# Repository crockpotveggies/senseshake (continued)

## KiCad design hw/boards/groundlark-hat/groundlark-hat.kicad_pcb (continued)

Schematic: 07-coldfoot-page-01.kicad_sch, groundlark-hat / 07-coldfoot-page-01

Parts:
C60, C61: 10u; Capacitor_SMD__C_0805_2012Metric; MPN GRM21BR61A106KE19L
C62, C67: 100n; Capacitor_SMD__C_0603_1608Metric; MPN GRM188R71H104KA93D
C63, C64, C65, C66: 22u; Capacitor_SMD__C_1206_3216Metric; MPN GRM31CR61A226KE19L
J5: Coldfoot run-1 1x1; Coldfoot_Run1_70DS; MPN HC-PBB40C-70DS-0.4V-3.0-02
L1: 4.7uH; Inductor_SMD__L_Bourns_SRN6045TA; MPN SRN6045TA-4R7M
R60: 0.1; Resistor_SMD__R_1206_3216Metric; MPN ERJ-8CWFR100V
U50: AP63203WU-7; Package_TO_SOT_SMD__TSOT-23-6; MPN AP63203WU-7

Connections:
28: J5.28 (analog[1].pad)
29: J5.29 (analog[0].pad)
CF_3V3: C66.1, C67.1, J5.9 (dvdd_pads[5].pad), J5.11 (vdd_pads[1].pad), J5.19 (dvdd_pads[4].pad), J5.24 (dvdd_pads[3].pad), J5.44 (dvdd_pads[2].pad), J5.46 (vdd_pads[0].pad), J5.54 (dvdd_pads[1].pad), J5.62 (dvdd_pads[0].pad), R60.2; also elsewhere on the board
CF_BIDIR_2: J5.4 (bidir[2].pad); also elsewhere on the board
CF_BIDIR_3: J5.3 (bidir[3].pad); also elsewhere on the board
CF_BIDIR_4: J5.2 (bidir[4].pad); also elsewhere on the board
CF_BIDIR_5: J5.1 (bidir[5].pad); also elsewhere on the board
CF_BIDIR_6: J5.70 (bidir[6].pad); also elsewhere on the board
CF_BIDIR_7: J5.69 (bidir[7].pad); also elsewhere on the board
CF_BIDIR_8: J5.68 (bidir[8].pad); also elsewhere on the board
CF_BIDIR_9: J5.67 (bidir[9].pad); also elsewhere on the board
CF_BIDIR_10: J5.66 (bidir[10].pad); also elsewhere on the board
CF_BIDIR_11: J5.65 (bidir[11].pad); also elsewhere on the board
CF_BIDIR_12: J5.64 (bidir[12].pad); also elsewhere on the board
CF_BIDIR_13: J5.63 (bidir[13].pad); also elsewhere on the board
CF_BIDIR_14: J5.60 (bidir[14].pad); also elsewhere on the board
CF_BIDIR_15: J5.59 (bidir[15].pad); also elsewhere on the board
CF_BIDIR_16: J5.58 (bidir[16].pad); also elsewhere on the board
CF_BIDIR_17: J5.57 (bidir[17].pad); also elsewhere on the board
CF_BIDIR_18: J5.56 (bidir[18].pad); also elsewhere on the board
CF_BIDIR_19: J5.55 (bidir[19].pad); also elsewhere on the board
CF_BIDIR_20: J5.52 (bidir[20].pad); also elsewhere on the board
CF_BIDIR_21: J5.51 (bidir[21].pad); also elsewhere on the board
CF_BIDIR_22: J5.50 (bidir[22].pad); also elsewhere on the board
CF_BIDIR_23: J5.49 (bidir[23].pad); also elsewhere on the board
CF_BIDIR_24: J5.48 (bidir[24].pad); also elsewhere on the board
CF_BIDIR_25: J5.47 (bidir[25].pad); also elsewhere on the board
CF_BIDIR_26: J5.43 (bidir[26].pad); also elsewhere on the board
CF_BIDIR_27: J5.42 (bidir[27].pad); also elsewhere on the board
CF_BIDIR_28: J5.41 (bidir[28].pad); also elsewhere on the board
CF_BIDIR_29: J5.40 (bidir[29].pad); also elsewhere on the board
CF_BIDIR_30: J5.39 (bidir[30].pad); also elsewhere on the board
CF_BIDIR_31: J5.38 (bidir[31].pad); also elsewhere on the board
CF_BIDIR_32: J5.37 (bidir[32].pad); also elsewhere on the board
CF_BIDIR_33: J5.36 (bidir[33].pad); also elsewhere on the board
CF_BIDIR_34: J5.35 (bidir[34].pad); also elsewhere on the board
CF_BIDIR_35: J5.34 (bidir[35].pad); also elsewhere on the board
CF_BIDIR_36: J5.33 (bidir[36].pad); also elsewhere on the board
CF_BIDIR_37: J5.32 (bidir[37].pad); also elsewhere on the board
CF_BIDIR_38: J5.31 (bidir[38].pad); also elsewhere on the board
CF_BIDIR_39: J5.30 (bidir[39].pad); also elsewhere on the board
CF_BST: C62.1, U50.6 (BST)
CF_IN_1: J5.26 (inputs[1].pad); also elsewhere on the board
CF_IN_2: J5.23 (inputs[2].pad); also elsewhere on the board
CF_IN_4: J5.21 (inputs[4].pad); also elsewhere on the board
CF_IN_5: J5.20 (inputs[5].pad); also elsewhere on the board
CF_IN_6: J5.17 (inputs[6].pad); also elsewhere on the board
CF_IN_7: J5.16 (inputs[7].pad); also elsewhere on the board
CF_IN_8: J5.15 (inputs[8].pad); also elsewhere on the board
CF_IN_9: J5.14 (inputs[9].pad); also elsewhere on the board
CF_IN_10: J5.13 (inputs[10].pad); also elsewhere on the board
CF_IN_11: J5.12 (inputs[11].pad); also elsewhere on the board
CF_MESH_CLK: J5.8 (clk_pad); also elsewhere on the board
CF_REG_3V3: C63.1, C64.1, C65.1, L1.2, R60.1, U50.1 (FB)
CF_RESET_N: J5.7 (rst_n_pad); also elsewhere on the board
CF_SW: C62.2, L1.1, U50.5 (SW)
CF_TELEMETRY: J5.5 (bidir[1].pad)
CF_TILE_CLK: J5.22 (inputs[3].pad); also elsewhere on the board
CF_UART_RX: J5.27 (inputs[0].pad); also elsewhere on the board
CF_UART_TX: J5.6 (bidir[0].pad); also elsewhere on the board
GND: C60.2, C61.2, C63.2, C64.2, C65.2, C66.2, C67.2, J5.10 (dvss_pads[0].pad), J5.18 (dvss_pads[0].pad), J5.25 (dvss_pads[0].pad), J5.45 (dvss_pads[0].pad), J5.53 (dvss_pads[0].pad), J5.61 (dvss_pads[0].pad), U50.4 (GND); also elsewhere on the board
PI_5V: C60.1, C61.1, U50.2 (EN), U50.3 (VIN); also elsewhere on the board

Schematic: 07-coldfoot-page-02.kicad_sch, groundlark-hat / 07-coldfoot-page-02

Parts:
C68, C69, C70, C71, C72, C73, C74, C75, C76: 100n; Capacitor_SMD__C_0603_1608Metric; MPN GRM188R71H104KA93D
R61: 47; Resistor_SMD__R_0603_1608Metric; MPN RC0603FR-0747RL
R62: 100k; Resistor_SMD__R_0603_1608Metric; MPN RC0603FR-07100KL
U51: TXU0202DCUR; Package_SO__VSSOP-8_2.3x2mm_P0.5mm; MPN TXU0202DCUR

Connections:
CF_3V3: C68.1, C69.1, C70.1, C71.1, C72.1, C73.1, C74.1, C76.1, U51.7 (VCCB); also elsewhere on the board
CF_IO_ENABLE: R62.1, U51.6 (OE); also elsewhere on the board
CF_UART_DRIVE: R61.1, U51.8 (B1Y_OUT)
CF_UART_RX: R61.2; also elsewhere on the board
CF_UART_TX: U51.1 (B2_IN); also elsewhere on the board
GND: C68.2, C69.2, C70.2, C71.2, C72.2, C73.2, C74.2, C75.2, C76.2, R62.2, U51.2 (GND); also elsewhere on the board
PI_3V3: C75.1, U51.3 (VCCA); also elsewhere on the board
PI_UART_RX: U51.4 (A2Y_OUT); also elsewhere on the board
PI_UART_TX: U51.5 (A1_IN); also elsewhere on the board

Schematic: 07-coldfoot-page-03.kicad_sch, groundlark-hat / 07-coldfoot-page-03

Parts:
C77, C78: 100n; Capacitor_SMD__C_0603_1608Metric; MPN GRM188R71H104KA93D
Q1: 2N7002; Package_TO_SOT_SMD__SOT-23; MPN 2N7002
R63, R64: 10k; Resistor_SMD__R_0603_1608Metric; MPN RC0603FR-0710KL
R65: 1k; Resistor_SMD__R_0603_1608Metric; MPN RC0603FR-071KL
R66: 100k; Resistor_SMD__R_0603_1608Metric; MPN RC0603FR-07100KL
R67, R68: 33; Resistor_SMD__R_0603_1608Metric; MPN RC0603FR-0733RL
U52: TLV803EA30DBZR; Package_TO_SOT_SMD__SOT-23; MPN TLV803EA30DBZR
Y1, Y2: 25MHz; Crystal__Crystal_SMD_3225-4Pin_3.2x2.5mm; MPN ASE-25.000MHZ-L-C-T

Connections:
CF_3V3: C77.1, C78.1, R63.2, R64.2, U52.3 (VDD), Y1.1 (ENABLE), Y1.4 (VDD), Y2.1 (ENABLE), Y2.4 (VDD); also elsewhere on the board
CF_MESH_CLK: R67.2; also elsewhere on the board
CF_MESH_CLK_RAW: R67.1, Y1.3 (OUT)
CF_RESET_GATE: Q1.1 (G), R65.2, R66.1
CF_RESET_GPIO: R65.1; also elsewhere on the board
CF_RESET_N: Q1.3 (D), R64.1, U52.2 (RESET_N); also elsewhere on the board
CF_TILE_CLK: R68.2; also elsewhere on the board
CF_TILE_CLK_RAW: R68.1, Y2.3 (OUT)
CF_UART_RX: R63.1; also elsewhere on the board
GND: C77.2, C78.2, Q1.2 (S), R66.2, U52.1 (GND), Y1.2 (GND), Y2.2 (GND); also elsewhere on the board

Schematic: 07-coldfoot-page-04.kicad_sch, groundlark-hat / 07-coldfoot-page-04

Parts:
C79: 100n; Capacitor_SMD__C_0603_1608Metric; MPN GRM188R71H104KA93D
R100, R101, R102, R103, R104, R105, R106, R107, R108, R109, R110: 100k; Resistor_SMD__R_0603_1608Metric; MPN RC0603FR-07100KL

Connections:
CF_3V3: C79.1; also elsewhere on the board
CF_BIDIR_2: R110.1; also elsewhere on the board
CF_IN_1: R100.1; also elsewhere on the board
CF_IN_2: R101.1; also elsewhere on the board
CF_IN_4: R102.1; also elsewhere on the board
CF_IN_5: R103.1; also elsewhere on the board
CF_IN_6: R104.1; also elsewhere on the board
CF_IN_7: R105.1; also elsewhere on the board
CF_IN_8: R106.1; also elsewhere on the board
CF_IN_9: R107.1; also elsewhere on the board
CF_IN_10: R108.1; also elsewhere on the board
CF_IN_11: R109.1; also elsewhere on the board
GND: C79.2, R100.2, R101.2, R102.2, R103.2, R104.2, R105.2, R106.2, R107.2, R108.2, R109.2, R110.2; also elsewhere on the board

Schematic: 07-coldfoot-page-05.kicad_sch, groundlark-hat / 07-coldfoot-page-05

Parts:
R111, R112, R113, R114, R115, R116, R117, R118, R119, R120, R121, R122: 100k; Resistor_SMD__R_0603_1608Metric; MPN RC0603FR-07100KL

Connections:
CF_3V3: R111.2, R122.2; also elsewhere on the board
CF_BIDIR_3: R111.1; also elsewhere on the board
CF_BIDIR_4: R112.1; also elsewhere on the board
CF_BIDIR_5: R113.1; also elsewhere on the board
CF_BIDIR_6: R114.1; also elsewhere on the board
CF_BIDIR_7: R115.1; also elsewhere on the board
CF_BIDIR_8: R116.1; also elsewhere on the board
CF_BIDIR_9: R117.1; also elsewhere on the board
CF_BIDIR_10: R118.1; also elsewhere on the board
CF_BIDIR_11: R119.1; also elsewhere on the board
CF_BIDIR_12: R120.1; also elsewhere on the board
CF_BIDIR_13: R121.1; also elsewhere on the board
CF_BIDIR_14: R122.1; also elsewhere on the board
GND: R112.2, R113.2, R114.2, R115.2, R116.2, R117.2, R118.2, R119.2, R120.2, R121.2; also elsewhere on the board

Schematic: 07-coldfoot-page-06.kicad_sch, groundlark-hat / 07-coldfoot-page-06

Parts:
R123, R124, R125, R126, R127, R128, R129, R130, R131, R132, R133, R134: 100k; Resistor_SMD__R_0603_1608Metric; MPN RC0603FR-07100KL

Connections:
CF_BIDIR_15: R123.1; also elsewhere on the board
CF_BIDIR_16: R124.1; also elsewhere on the board
CF_BIDIR_17: R125.1; also elsewhere on the board
CF_BIDIR_18: R126.1; also elsewhere on the board
CF_BIDIR_19: R127.1; also elsewhere on the board
CF_BIDIR_20: R128.1; also elsewhere on the board
CF_BIDIR_21: R129.1; also elsewhere on the board
CF_BIDIR_22: R130.1; also elsewhere on the board
CF_BIDIR_23: R131.1; also elsewhere on the board
CF_BIDIR_24: R132.1; also elsewhere on the board
CF_BIDIR_25: R133.1; also elsewhere on the board
CF_BIDIR_26: R134.1; also elsewhere on the board
GND: R123.2, R124.2, R125.2, R126.2, R127.2, R128.2, R129.2, R130.2, R131.2, R132.2, R133.2, R134.2; also elsewhere on the board

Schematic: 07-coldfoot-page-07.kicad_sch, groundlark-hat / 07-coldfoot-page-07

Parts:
R135, R136, R137, R138, R139, R140, R141, R142, R143, R144, R145, R146: 100k; Resistor_SMD__R_0603_1608Metric; MPN RC0603FR-07100KL

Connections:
CF_3V3: R135.2, R141.2; also elsewhere on the board
CF_BIDIR_27: R135.1; also elsewhere on the board
CF_BIDIR_28: R136.1; also elsewhere on the board
CF_BIDIR_29: R137.1; also elsewhere on the board
CF_BIDIR_30: R138.1; also elsewhere on the board
CF_BIDIR_31: R139.1; also elsewhere on the board
CF_BIDIR_32: R140.1; also elsewhere on the board
CF_BIDIR_33: R141.1; also elsewhere on the board
CF_BIDIR_34: R142.1; also elsewhere on the board
CF_BIDIR_35: R143.1; also elsewhere on the board
CF_BIDIR_36: R144.1; also elsewhere on the board
CF_BIDIR_37: R145.1; also elsewhere on the board
CF_BIDIR_38: R146.1; also elsewhere on the board
GND: R136.2, R137.2, R138.2, R139.2, R140.2, R142.2, R143.2, R144.2, R145.2, R146.2; also elsewhere on the board

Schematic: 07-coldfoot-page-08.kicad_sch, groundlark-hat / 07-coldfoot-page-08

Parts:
R147: 100k; Resistor_SMD__R_0603_1608Metric; MPN RC0603FR-07100KL

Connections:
CF_BIDIR_39: R147.1; also elsewhere on the board
GND: R147.2; also elsewhere on the board

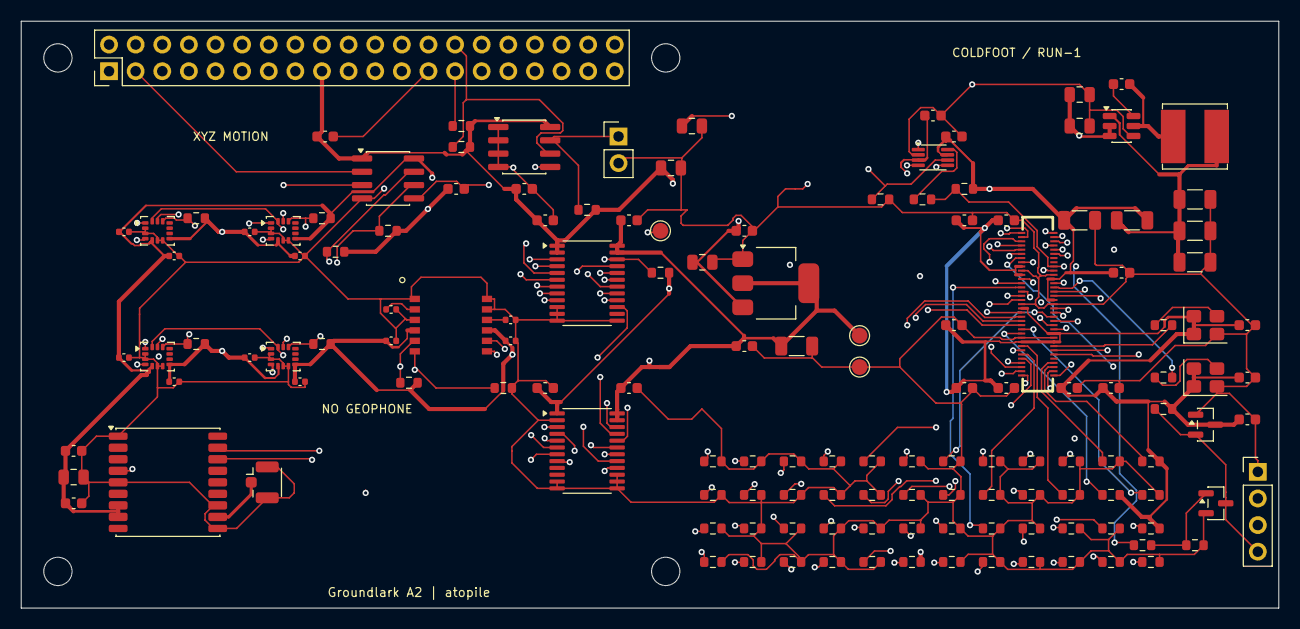
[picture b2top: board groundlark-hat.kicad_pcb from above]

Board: 6 copper layers, 120.0 x 56.0 mm, 147 parts (0 on the bottom side), 106 nets.

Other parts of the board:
H1, H2, H3, H4: M2.5 NPTH; MountingHole__MountingHole_2.7mm_M2.5

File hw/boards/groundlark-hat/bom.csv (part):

Reference,Value,MPN,Footprint,DNP,Note
J1,Raspberry Pi 40-pin,Samtec ESQ-120-23-G-D,Connector_PinHeader_2.54mm__PinHeader_2x20_P2.54mm_Vertical,False,"Header land pattern matches bottom mounted socket top-view numbering; tall stack, check Pi 4/5 cooler clearance."
U1,24LC32A,24LC32A-I/SN,Package_SO__SOIC-8_3.9x4.9mm_P1.27mm,False,
R1,3.9k,RC0603FR-073K9L,Resistor_SMD__R_0603_1608Metric,False,
R2,3.9k,RC0603FR-073K9L,Resistor_SMD__R_0603_1608Metric,False,
R3,1k,RC0603FR-071KL,Resistor_SMD__R_0603_1608Metric,False,
JP1,EEPROM write enable,EEPROM write enable,Connector_PinHeader_2.54mm__PinHeader_1x02_P2.54mm_Vertical,False,Fit shunt only while programming ID EEPROM.
C1,100n,GRM188R71H104KA93D,Capacitor_SMD__C_0603_1608Metric,False,
C2,10u,GRM21BR61A106KE19L,Capacitor_SMD__C_0805_2012Metric,False,
C3,10u,GRM21BR61A106KE19L,Capacitor_SMD__C_0805_2012Metric,False,
U11,LSM6DSOTR,LSM6DSOTR,Package_LGA__LGA-14_3x2.5mm_P0.5mm_LayoutBorder3x4y,False,
C12,100n,GRM155R71C104KA88D,Capacitor_SMD__C_0402_1005Metric,False,
C13,100n,GRM155R71C104KA88D,Capacitor_SMD__C_0402_1005Metric,False,
R11,10k,RC0603FR-0710KL,Resistor_SMD__R_0603_1608Metric,False,
U12,LSM6DSOTR,LSM6DSOTR,Package_LGA__LGA-14_3x2.5mm_P0.5mm_LayoutBorder3x4y,False,
C14,100n,GRM155R71C104KA88D,Capacitor_SMD__C_0402_1005Metric,False,
C15,100n,GRM155R71C104KA88D,Capacitor_SMD__C_0402_1005Metric,False,
R12,10k,RC0603FR-0710KL,Resistor_SMD__R_0603_1608Metric,False,
U13,LSM6DSOTR,LSM6DSOTR,Package_LGA__LGA-14_3x2.5mm_P0.5mm_LayoutBorder3x4y,False,
C16,100n,GRM155R71C104KA88D,Capacitor_SMD__C_0402_1005Metric,False,
C17,100n,GRM155R71C104KA88D,Capacitor_SMD__C_0402_1005Metric,False,
R13,10k,RC0603FR-0710KL,Resistor_SMD__R_0603_1608Metric,False,
U14,LSM6DSOTR,LSM6DSOTR,Package_LGA__LGA-14_3x2.5mm_P0.5mm_LayoutBorder3x4y,False,
C18,100n,GRM155R71C104KA88D,Capacitor_SMD__C_0402_1005Metric,False,
C19,100n,GRM155R71C104KA88D,Capacitor_SMD__C_0402_1005Metric,False,
R14,10k,RC0603FR-0710KL,Resistor_SMD__R_0603_1608Metric,False,
U20,SCL3300-D01,SCL3300-D01-10,Groundlark__SCL3300_D01,False,
C20,100n,GRM155R71C104KA88D,Capacitor_SMD__C_0402_1005Metric,False,
C21,100n,GRM155R71C104KA88D,Capacitor_SMD__C_0402_1005Metric,False,
C22,100n,GRM155R71C104KA88D,Capacitor_SMD__C_0402_1005Metric,False,
C23,100n,GRM155R71C104KA88D,Capacitor_SMD__C_0402_1005Metric,False,
R20,10k,RC0603FR-0710KL,Resistor_SMD__R_0603_1608Metric,False,
U21,MAX-M10S,MAX-M10S-00B,RF_GPS__ublox_MAX,False,I2C 0x42. Passive external GNSS antenna; no DC bias at RF connector.
C24,100n,GRM188R71H104KA93D,Capacitor_SMD__C_0603_1608Metric,False,
C25,4.7u,GRM21BR71A475KA73L,Capacitor_SMD__C_0805_2012Metric,False,
C26,100n,GRM188R71H104KA93D,Capacitor_SMD__C_0603_1608Metric,False,
J2,Passive GNSS antenna,U.FL-R-SMT-1(10),Connector_Coaxial__U.FL_Hirose_U.FL-R-SMT-1_Vertical,False,50 ohm line; external passive antenna.
J4,Coldfoot test UART/reset,Coldfoot UART service ONLY,Connector_PinHeader_2.54mm__PinHeader_1x04_P2.54mm_Vertical,False,Test points for assembled module UART and active-low reset; do not connect a second driving host.
H1,M2.5 NPTH,M2.5 NPTH,MountingHole__MountingHole_2.7mm_M2.5,False,Nonmagnetic standoffs.
H2,M2.5 NPTH,M2.5 NPTH,MountingHole__MountingHole_2.7mm_M2.5,False,Nonmagnetic standoffs.
H3,M2.5 NPTH,M2.5 NPTH,MountingHole__MountingHole_2.7mm_M2.5,False,Nonmagnetic standoffs.
H4,M2.5 NPTH,M2.5 NPTH,MountingHole__MountingHole_2.7mm_M2.5,False,Nonmagnetic standoffs.
U40,TLV1117LV33DCYR,TLV1117LV33DCYR,Package_TO_SOT_SMD__SOT-223-3_TabPin2,False,
C40,10u,GRM21BR61A106KE19L,Capacitor_SMD__C_0805_2012Metric,False,
C41,100n,GRM188R71H104KA93D,Capacitor_SMD__C_0603_1608Metric,False,
C42,22u,GRM31CR61A226KE19L,Capacitor_SMD__C_1206_3216Metric,False,
C43,100n,GRM188R71H104KA93D,Capacitor_SMD__C_0603_1608Metric,False,
U41,SN74LVC8T245PWR,SN74LVC8T245PWR,Package_SO__TSSOP-24_4.4x7.8mm_P0.65mm,False,
U42,SN74LVC8T245PWR,SN74LVC8T245PWR,Package_SO__TSSOP-24_4.4x7.8mm_P0.65mm,False,
C44,100n,GRM188R71H104KA93D,Capacitor_SMD__C_0603_1608Metric,False,
C45,100n,GRM188R71H104KA93D,Capacitor_SMD__C_0603_1608Metric,False,
C46,100n,GRM188R71H104KA93D,Capacitor_SMD__C_0603_1608Metric,False,
C47,100n,GRM188R71H104KA93D,Capacitor_SMD__C_0603_1608Metric,False,
R50,10k,RC0603FR-0710KL,Resistor_SMD__R_0603_1608Metric,False,
R51,100k,RC0603FR-07100KL,Resistor_SMD__R_0603_1608Metric,False,
U43,ISO1640BDR,ISO1640BDR,Package_SO__SOIC-8_3.9x4.9mm_P1.27mm,False,Power-domain isolation only: grounds are joined. Side-1 VOL max 0.71V requires host VIL >=0.8V; verify Pi revision.
C48,100n,GRM188R71H104KA93D,Capacitor_SMD__C_0603_1608Metric,False,
C49,100n,GRM188R71H104KA93D,Capacitor_SMD__C_0603_1608Metric,False,
R52,4.7k,RC0603FR-074K7L,Resistor_SMD__R_0603_1608Metric,False,
R53,4.7k,RC0603FR-074K7L,Resistor_SMD__R_0603_1608Metric,False,
TP1,SENS_3V3,SENS_3V3,TestPoint__TestPoint_Pad_D1.5mm,False,
TP2,GND,GND,TestPoint__TestPoint_Pad_D1.5mm,False,
TP4,SENSOR_OE_N,SENSOR_OE_N,TestPoint__TestPoint_Pad_D1.5mm,False,
J5,Coldfoot run-1 1x1,HC-PBB40C-70DS-0.4V-3.0-02,Coldfoot_Run1_70DS,False,"14x16mm run-1 module, 3mm mating height; actual connector nets audited against slot_1x1.yaml."
U50,AP63203WU-7,AP63203WU-7,Package_TO_SOT_SMD__TSOT-23-6,False,
L1,4.7uH,SRN6045TA-4R7M,Inductor_SMD__L_Bourns_SRN6045TA,False,"4.7uH ±20%, DCR 26mOhm ±20%, Irms 4.5A, Isat 6.8A. Selected within regulator 2.2–10uH range."
C60,10u,GRM21BR61A106KE19L,Capacitor_SMD__C_0805_2012Metric,False,
C61,10u,GRM21BR61A106KE19L,Capacitor_SMD__C_0805_2012Metric,False,
C62,100n,GRM188R71H104KA93D,Capacitor_SMD__C_0603_1608Metric,False,
C63,22u,GRM31CR61A226KE19L,Capacitor_SMD__C_1206_3216Metric,False,
C64,22u,GRM31CR61A226KE19L,Capacitor_SMD__C_1206_3216Metric,False,
C65,22u,GRM31CR61A226KE19L,Capacitor_SMD__C_1206_3216Metric,False,
R60,0.1,ERJ-8CWFR100V,Resistor_SMD__R_1206_3216Metric,False,0.1 ohm current shunt. 0.6A total carrier load envelope; module core contacts limited to 0.5A combined.
C66,22u,GRM31CR61A226KE19L,Capacitor_SMD__C_1206_3216Metric,False,
C67,100n,GRM188R71H104KA93D,Capacitor_SMD__C_0603_1608Metric,False,
C68,100n,GRM188R71H104KA93D,Capacitor_SMD__C_0603_1608Metric,False,
C69,100n,GRM188R71H104KA93D,Capacitor_SMD__C_0603_1608Metric,False,
C70,100n,GRM188R71H104KA93D,Capacitor_SMD__C_0603_1608Metric,False,
C71,100n,GRM188R71H104KA93D,Capacitor_SMD__C_0603_1608Metric,False,
C72,100n,GRM188R71H104KA93D,Capacitor_SMD__C_0603_1608Metric,False,
C73,100n,GRM188R71H104KA93D,Capacitor_SMD__C_0603_1608Metric,False,
C74,100n,GRM188R71H104KA93D,Capacitor_SMD__C_0603_1608Metric,False,
U51,TXU0202DCUR,TXU0202DCUR,Package_SO__VSSOP-8_2.3x2mm_P0.5mm,False,
C75,100n,GRM188R71H104KA93D,Capacitor_SMD__C_0603_1608Metric,False,
C76,100n,GRM188R71H104KA93D,Capacitor_SMD__C_0603_1608Metric,False,
R61,47,RC0603FR-0747RL,Resistor_SMD__R_0603_1608Metric,False,
R62,100k,RC0603FR-07100KL,Resistor_SMD__R_0603_1608Metric,False,
R63,10k,RC0603FR-0710KL,Resistor_SMD__R_0603_1608Metric,False,
U52,TLV803EA30DBZR,TLV803EA30DBZR,Package_TO_SOT_SMD__SOT-23,False,"3.0V falling threshold, 200ms nominal release delay; open-drain output."
C77,100n,GRM188R71H104KA93D,Capacitor_SMD__C_0603_1608Metric,False,
R64,10k,RC0603FR-0710KL,Resistor_SMD__R_0603_1608Metric,False,
Q1,2N7002,2N7002,Package_TO_SOT_SMD__SOT-23,False,Pi GPIO17 HIGH asserts chip reset; does not drive a live voltage into unpowered chip.
R65,1k,RC0603FR-071KL,Resistor_SMD__R_0603_1608Metric,False,
R66,100k,RC0603FR-07100KL,Resistor_SMD__R_0603_1608Metric,False,
Y1,25MHz,ASE-25.000MHZ-L-C-T,Crystal__Crystal_SMD_3225-4Pin_3.2x2.5mm,False,
R67,33,RC0603FR-0733RL,Resistor_SMD__R_0603_1608Metric,False,
C78,100n,GRM188R71H104KA93D,Capacitor_SMD__C_0603_1608Metric,False,
Y2,25MHz,ASE-25.000MHZ-L-C-T,Crystal__Crystal_SMD_3225-4Pin_3.2x2.5mm,False,
R68,33,RC0603FR-0733RL,Resistor_SMD__R_0603_1608Metric,False,
C79,100n,GRM188R71H104KA93D,Capacitor_SMD__C_0603_1608Metric,False,
R100,100k,RC0603FR-07100KL,Resistor_SMD__R_0603_1608Metric,False,
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
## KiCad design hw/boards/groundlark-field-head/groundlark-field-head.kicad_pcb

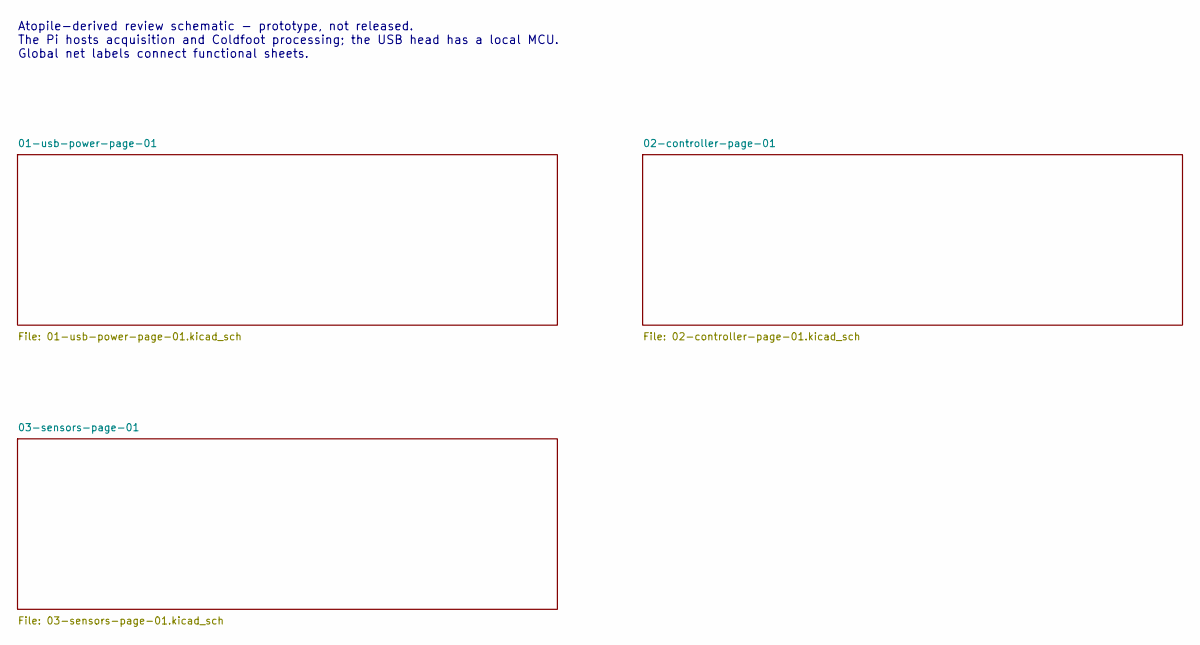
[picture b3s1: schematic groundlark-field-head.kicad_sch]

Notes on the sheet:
Atopile-derived review schematic - prototype, not released. The Pi hosts acquisition and Coldfoot processing; the USB head has a local MCU. Global net labels connect functional sheets.

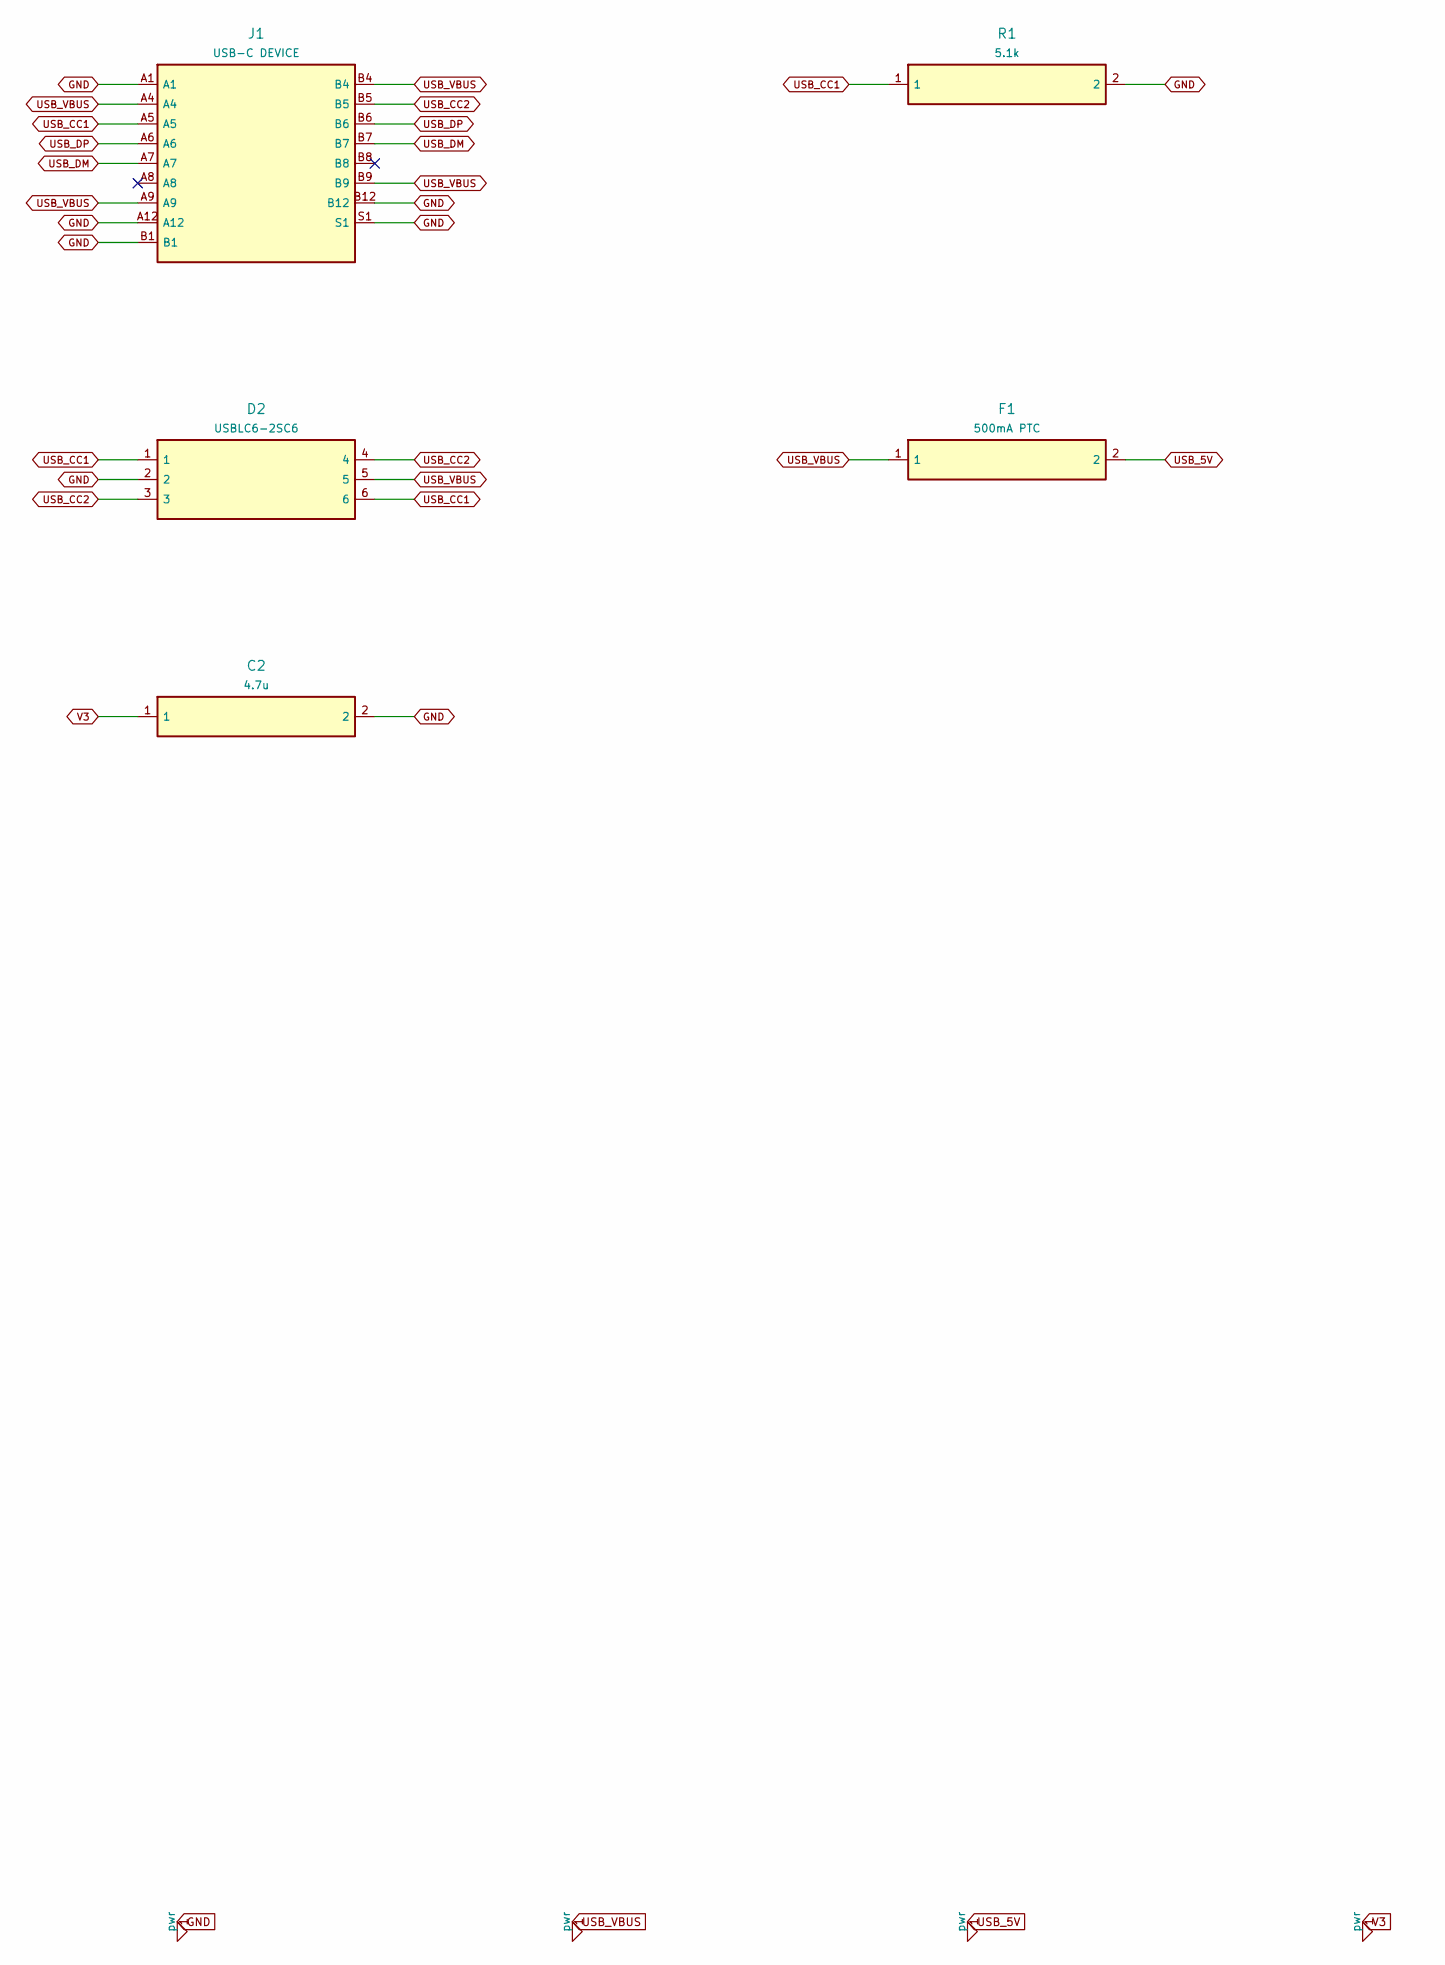
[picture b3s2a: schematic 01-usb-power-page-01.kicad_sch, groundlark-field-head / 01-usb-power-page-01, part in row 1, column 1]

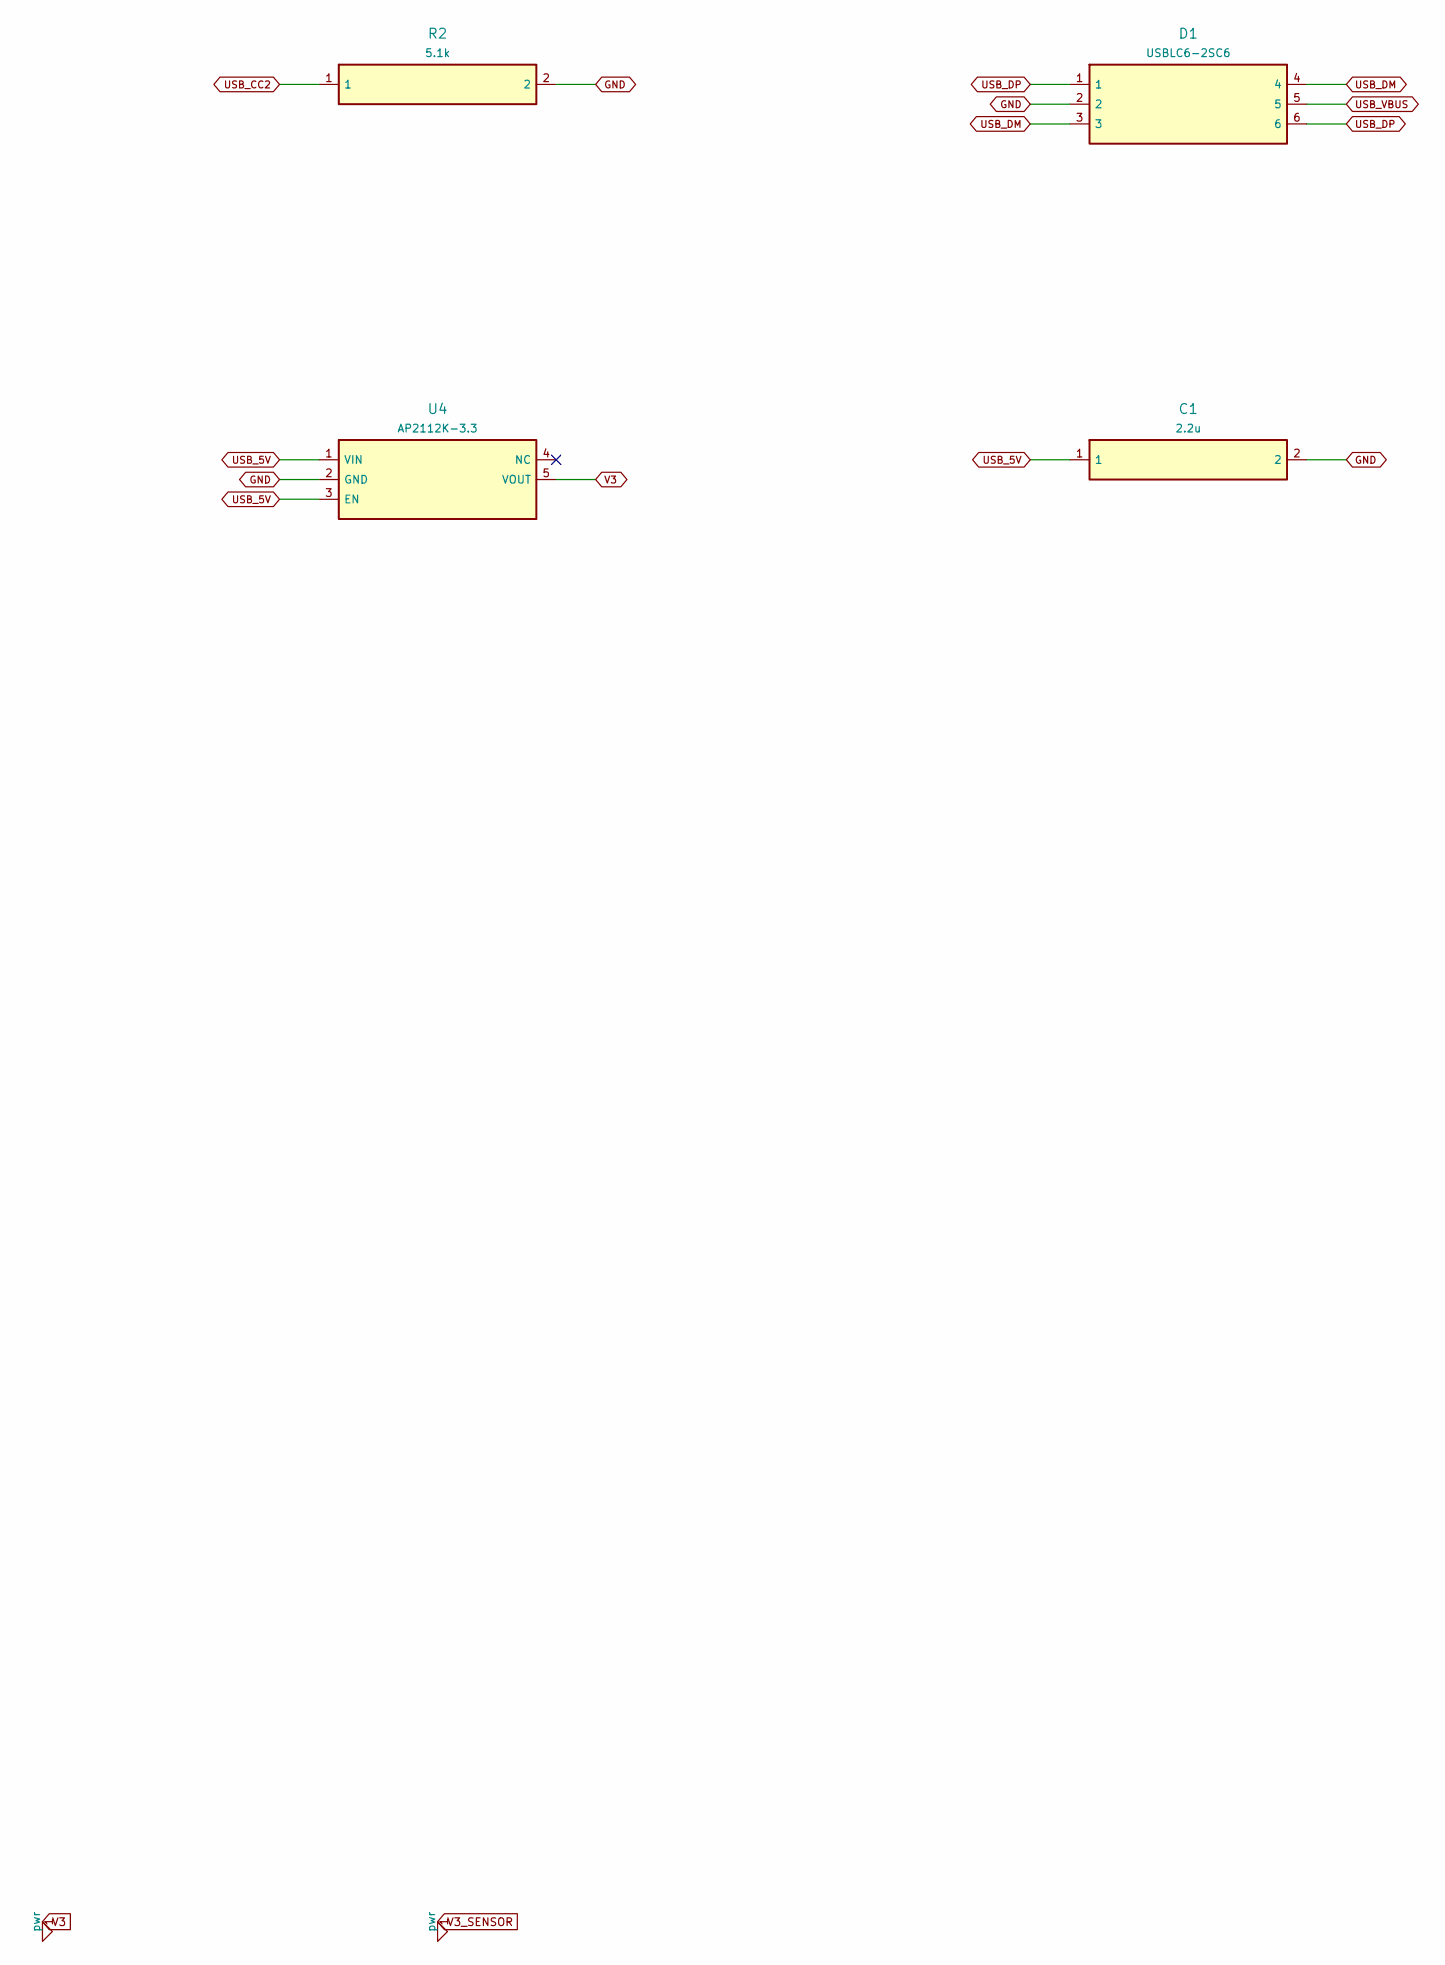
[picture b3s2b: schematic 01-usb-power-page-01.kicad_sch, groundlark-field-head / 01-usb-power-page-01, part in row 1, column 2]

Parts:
C1: 2.2u; Capacitor_SMD__C_0805_2012Metric; MPN GRM21BR71E225KA73L
C2: 4.7u; Capacitor_SMD__C_0805_2012Metric; MPN GRM21BR71A475KA73L
D1, D2: USBLC6-2SC6; Package_TO_SOT_SMD__SOT-23-6; MPN USBLC6-2SC6
F1: 500mA PTC; Fuse__Fuse_1812_4532Metric; MPN MF-MSMF050-2
J1: USB-C DEVICE; Connector_USB__USB_C_Receptacle_GCT_USB4105-xx-A_16P_TopMnt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; MPN USB4105-GF-A
R1, R2: 5.1k; Resistor_SMD__R_0603_1608Metric; MPN RC0603FR-075K1L
U4: AP2112K-3.3; Package_TO_SOT_SMD__SOT-23-5; MPN AP2112K-3.3TRG1

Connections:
4: U4.4 (NC)
A8: J1.A8
B8: J1.B8
GND: C1.2, C2.2, D1.2, D2.2, J1.A1, J1.A12, J1.B1, J1.B12, J1.S1, R1.2, R2.2, U4.2 (GND); also elsewhere on the board
USB_5V: C1.1, F1.2, U4.1 (VIN), U4.3 (EN)
USB_CC1: D2.1, D2.6, J1.A5, R1.1
USB_CC2: D2.3, D2.4, J1.B5, R2.1
USB_DM: D1.3, D1.4, J1.A7, J1.B7; also elsewhere on the board
USB_DP: D1.1, D1.6, J1.A6, J1.B6; also elsewhere on the board
USB_VBUS: D1.5, D2.5, F1.1, J1.A4, J1.A9, J1.B4, J1.B9
V3: C2.1, U4.5 (VOUT); also elsewhere on the board

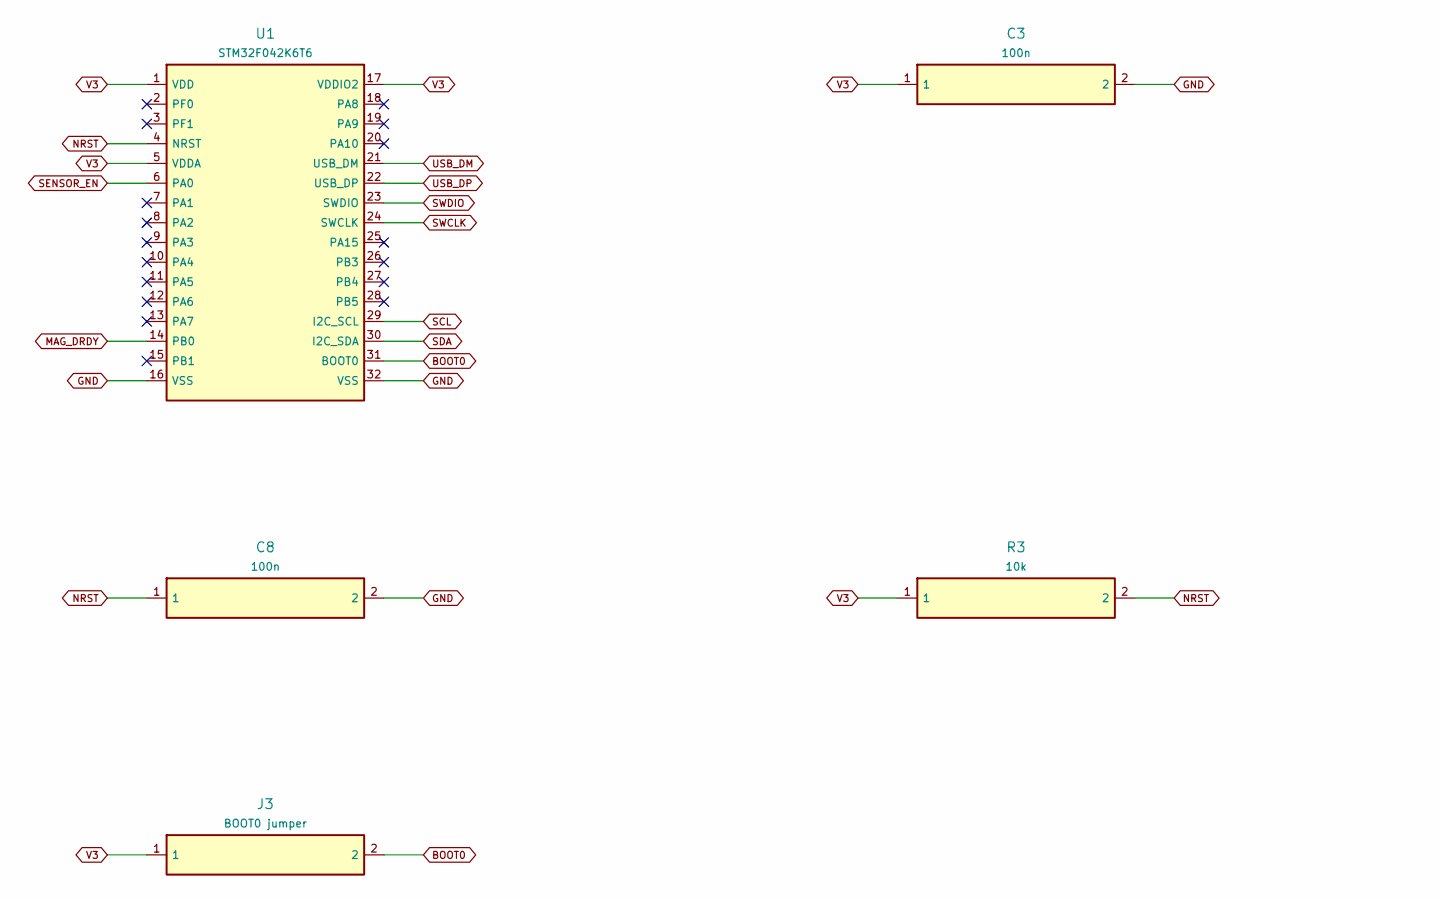
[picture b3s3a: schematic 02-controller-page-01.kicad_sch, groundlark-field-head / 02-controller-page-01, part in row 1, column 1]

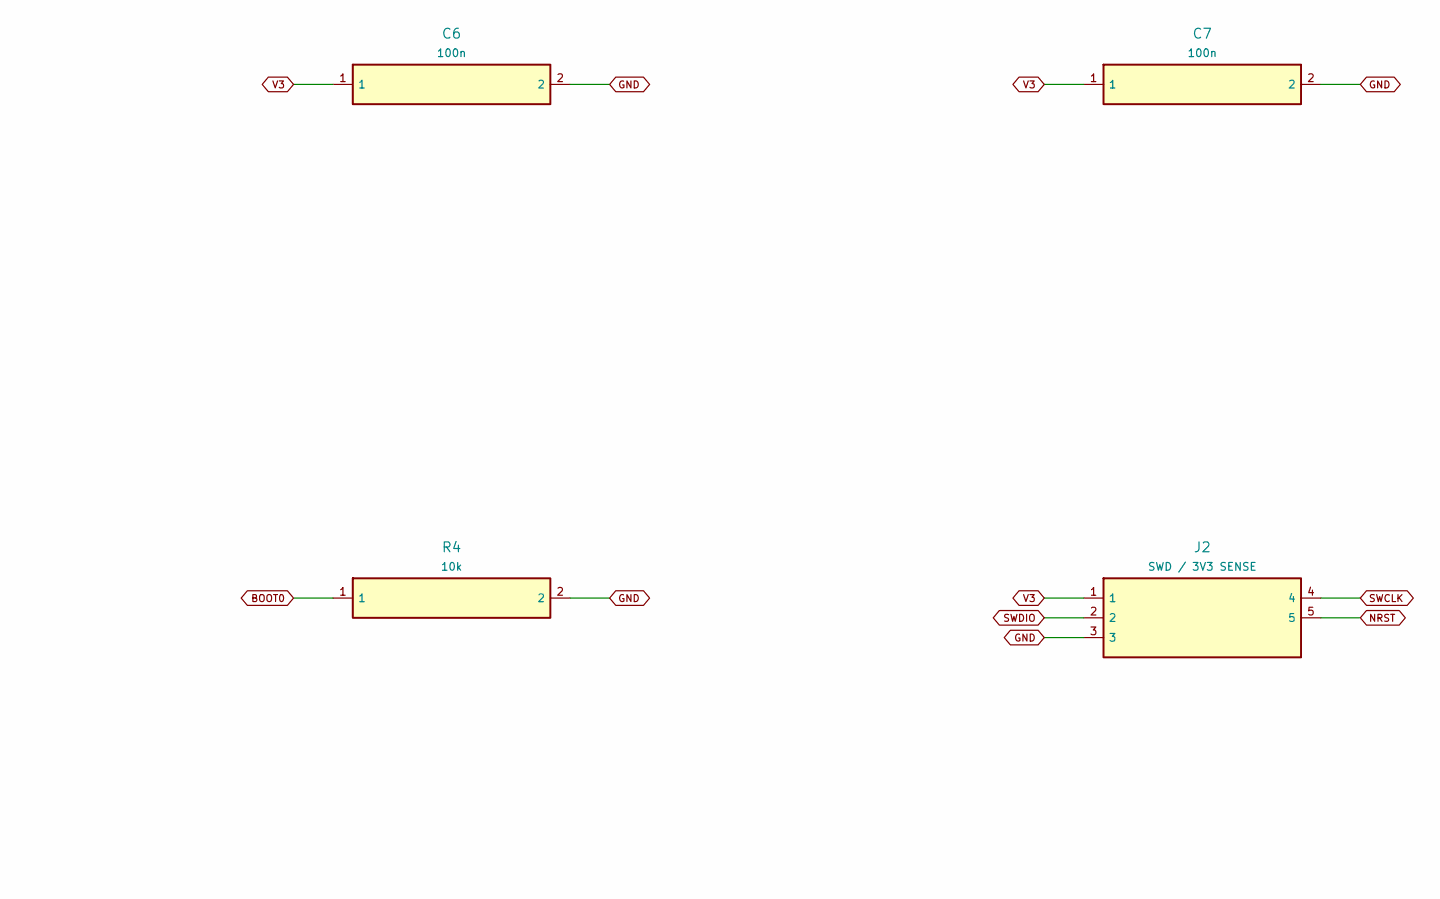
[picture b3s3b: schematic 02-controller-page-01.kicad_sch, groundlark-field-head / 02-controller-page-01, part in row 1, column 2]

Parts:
C3, C6, C7, C8: 100n; Capacitor_SMD__C_0603_1608Metric; MPN GRM188R71H104KA93D
J2: SWD / 3V3 SENSE; Connector_PinHeader_2.54mm__PinHeader_1x05_P2.54mm_Vertical; MPN M20-9990545
J3: BOOT0 jumper; Connector_PinHeader_2.54mm__PinHeader_1x02_P2.54mm_Vertical; MPN EEPROM write enable
R3, R4: 10k; Resistor_SMD__R_0603_1608Metric; MPN RC0603FR-0710KL
U1: STM32F042K6T6; Package_QFP__LQFP-32_7x7mm_P0.8mm; MPN STM32F042K6T6

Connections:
2: U1.2 (PF0)
3: U1.3 (PF1)
7: U1.7 (PA1)
8: U1.8 (PA2)
9: U1.9 (PA3)
10: U1.10 (PA4)
11: U1.11 (PA5)
12: U1.12 (PA6)
13: U1.13 (PA7)
15: U1.15 (PB1)
18: U1.18 (PA8)
19: U1.19 (PA9)
20: U1.20 (PA10)
25: U1.25 (PA15)
26: U1.26 (PB3)
27: U1.27 (PB4)
28: U1.28 (PB5)
BOOT0: J3.2, R4.1, U1.31 (BOOT0)
GND: C3.2, C6.2, C7.2, C8.2, J2.3, R4.2, U1.16 (VSS), U1.32 (VSS); also elsewhere on the board
MAG_DRDY: U1.14 (PB0); also elsewhere on the board
NRST: C8.1, J2.5, R3.2, U1.4 (NRST)
SCL: U1.29 (I2C_SCL); also elsewhere on the board
SDA: U1.30 (I2C_SDA); also elsewhere on the board
SENSOR_EN: U1.6 (PA0); also elsewhere on the board
SWCLK: J2.4, U1.24 (SWCLK)
SWDIO: J2.2, U1.23 (SWDIO)
USB_DM: U1.21 (USB_DM); also elsewhere on the board
USB_DP: U1.22 (USB_DP); also elsewhere on the board
V3: C3.1, C6.1, C7.1, J2.1, J3.1, R3.1, U1.1 (VDD), U1.5 (VDDA), U1.17 (VDDIO2); also elsewhere on the board
